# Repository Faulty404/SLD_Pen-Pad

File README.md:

# Pen-Pad for SLD Students
The aim of this project is to develop and smart pen and a writing pad for students having SLDs(Special Learning Disabilities) by intergrating assitive technology to aid their learning.

# Ideation

To build a pen and pad for students with SLDs, we must first understand what these SLDs are and how we can include assistive technology to aid them in the learning process.

# Implementation

The project repository contians the KiCad design for the PCB that will be placed inside the smart pen. 

It contains an ESP32 connected to a mic and a bluetooth module to communicate with a Raspberry Pi Compute to send audio data.

The Raspberry Pi Compute has an onboard offline Machine Learning Model called VOSK, which converts audio to text.

# Technolgies Used

- IOT (Internet of Things)
- Machine Learning
- PCB and electronic design

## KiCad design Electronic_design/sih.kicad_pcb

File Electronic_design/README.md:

# Schematic and PCB design for an ESP32-based smart pen circuit. 

The circuit uses an LM358 op-amp to amplify signals from a microphone and includes battery charging capabilities using the TP4057 charger IC.

ESP32-D0WD: The main microcontroller chip used for processing and wireless communication.

AP2112K-3.3: A 3.3V linear voltage regulator providing stable power to the ESP32.

TP4057: A lithium-ion battery charger IC for charging a 3.7V LiPo battery.

LM358: Operational amplifier used to amplify the microphone signal.

Microphone: Used to capture audio input from the user.

The gain of the op-amp can be adjusted using the potentiometer.

This basic circuit aims at taking input using microphone(on the body of smart pen) from the user and processing it to the ESP 32 which has bluetooth module used to send the text to speech code to the smart board connected.

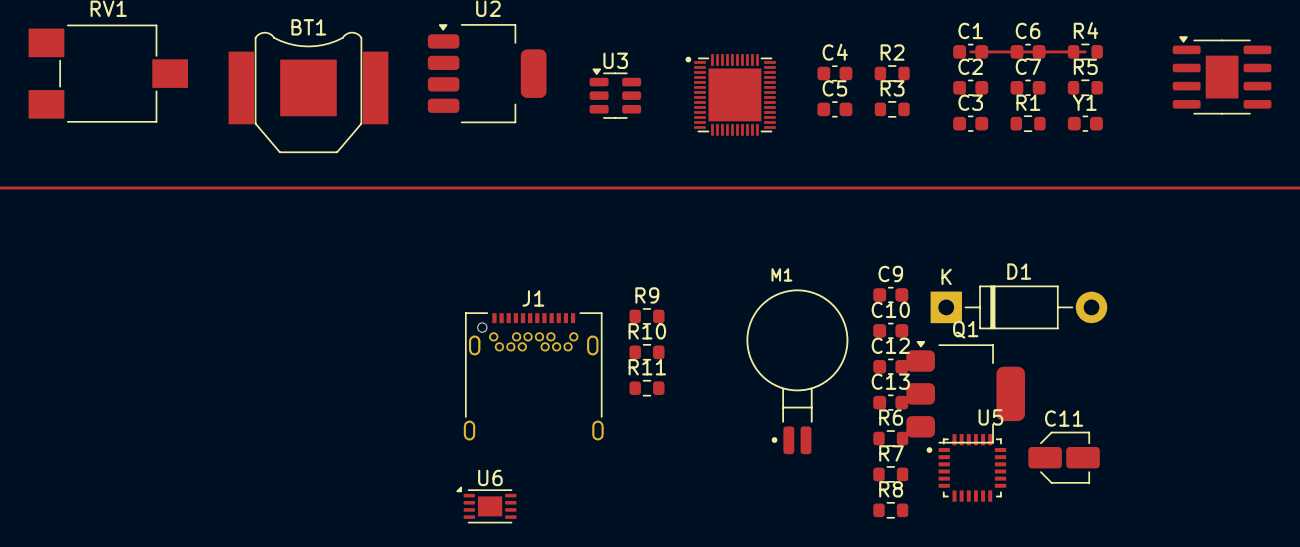
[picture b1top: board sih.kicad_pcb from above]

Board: 2 copper layers, 37 parts (0 on the bottom side), 29 nets, no tracks yet.

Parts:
BT1: 3.7V; BatteryHolder_Keystone_2998_1x6.8mm
C1, C2, C5, C7, C12: 100n; C_0603_1608Metric
C3, C10: 0.1u; C_0603_1608Metric
C4, C9, C13: 10u; C_0603_1608Metric
C6: 1u; C_0603_1608Metric
C11: C_Polarized; C_Elec_3x5.4
D1: 1N5819; D_DO-41_SOD81_P10.16mm_Horizontal
J1: USB_C_Receptacle_PowerOnly_6P; USB_C_Receptacle_Amphenol_12401548E4-2A
M1: C0720B001F; XDCR_C0720B001F
MK1: Microphone; DINRailAdapter_3xM3_PhoenixContact_1201578
Q1: IRLZ44N; SOT-223
R1: 10K; R_0603_1608Metric
R2: 2.2k; R_0603_1608Metric
R3, R4, R8: 10k; R_0603_1608Metric
R5: 100k; R_0603_1608Metric
R6, R7: 4.7k; R_0603_1608Metric
R9, R10: 5.1k; R_0603_1608Metric
R11: R_prog; R_0603_1608Metric
RV1: 10 K; Potentiometer_ACP_CA6-VSMD_Vertical
U1: ESP32-D0WD; QFN35P500X500X90-49N
U2: AP2112K-3.3; SOT-223-5
U3: TP4057; SOT-23-6
U4: LM358; SOIC-8-1EP_3.9x4.9mm_P1.27mm_EP2.29x3mm
U5: MPU-6050; QFN50P400X400X95-24N
U6: MCP73831-2-MC; DFN-8-1EP_3x2mm_P0.5mm_EP1.7x1.4mm
Y1: 40MHz; C_0603_1608Metric

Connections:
5v: C3.2, J1.A9 (VBUS), J1.B9 (VBUS), R1.1, U2.1 (VIN), U3.4 (V_{CC})
GND: C1.1, C2.1, C3.1, C4.2, C7.1, C10.2, C12.1, C13.1, J1.A12 (GND), J1.B12 (GND), J1.S1 (SHIELD), Q1.3 (S), R4.1, R9.2, R10.2, R11.2, U1.23 (GPIO0), U1.49 (GND), U2.2 (GND), U3.2 (GND), U3.5 (STDBY), U5.18 (GND)
unnamed: BT1.1 (+), U3.3 (BAT)
unnamed: BT1.2 (-), C4.1
unnamed: C5.2, R5.2, U4.1
unnamed: C9.2, C10.1
unnamed: C9.1, C11.1, C12.2, C13.2, D1.2 (A), M1.1 (V+), R2.2, R3.1, R6.2, R7.2, U1.3 (VDD3P3), U1.4 (VDD3P3), U2.5 (VOUT), U5.13 (VDD)
unnamed: C11.2, D1.1 (K), M1.2 (V-), Q1.2 (D)
unnamed: J1.A5 (CC1), R9.1
unnamed: J1.B5 (CC2), R10.1
unnamed: C6.2, R2.1, RV1.3
unnamed: Q1.1 (G), R8.1
unnamed: C2.2, U1.48 (CAP1)
unnamed: C1.2, U1.47 (CAP2)
unnamed: U1.24 (GPIO4), U5.12 (INT)
unnamed: R8.2, U1.25 (GPIO16)
unnamed: R7.1, U1.42 (GPIO21), U5.24 (SDA)
unnamed: R6.1, U1.39 (GPIO22), U5.23 (SCL)
unnamed: C5.1, U1.36 (GPIO23)
unnamed: U1.1 (VDDA), U1.43 (VDDA), U1.46 (VDDA)
unnamed: U1.44 (XTAL_N), Y1.2
unnamed: U1.45 (XTAL_P), Y1.1
unnamed: R1.2, U2.3 (EN)
unnamed: R11.1, U3.6 (PROG)
unnamed: C7.2, R3.2, R4.2, RV1.2, U4.3 (+)
unnamed: C6.1, R5.1, RV1.1, U4.2 (-)
unnamed: U5.2 (NC), U5.3 (NC), U5.4 (NC), U5.5 (NC), U5.14 (NC), U5.15 (NC), U5.16 (NC), U5.17 (NC)
unnamed: U6.3 (V_{BAT}), U6.4 (V_{BAT})
unnamed: U6.1 (V_{DD}), U6.2 (V_{DD})

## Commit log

2024-08-31 Uploading PCB design and schematic for stylus
2024-08-31 Create README.md
    README for the PCB
2024-08-31 Adding code to implement bluetooth audio sync between esp32 and raspberry pi using espidf
2024-08-31 PCB design and schematic modified
2024-08-31 Update README.md
    Update README.md in Electronic_design
2024-08-31 Updating README
2024-09-14 Adding the basic notes taking interface using Qt6
2024-09-14 Updated design with all components
2024-09-15 Adding ruled and grid page system to Notes app
